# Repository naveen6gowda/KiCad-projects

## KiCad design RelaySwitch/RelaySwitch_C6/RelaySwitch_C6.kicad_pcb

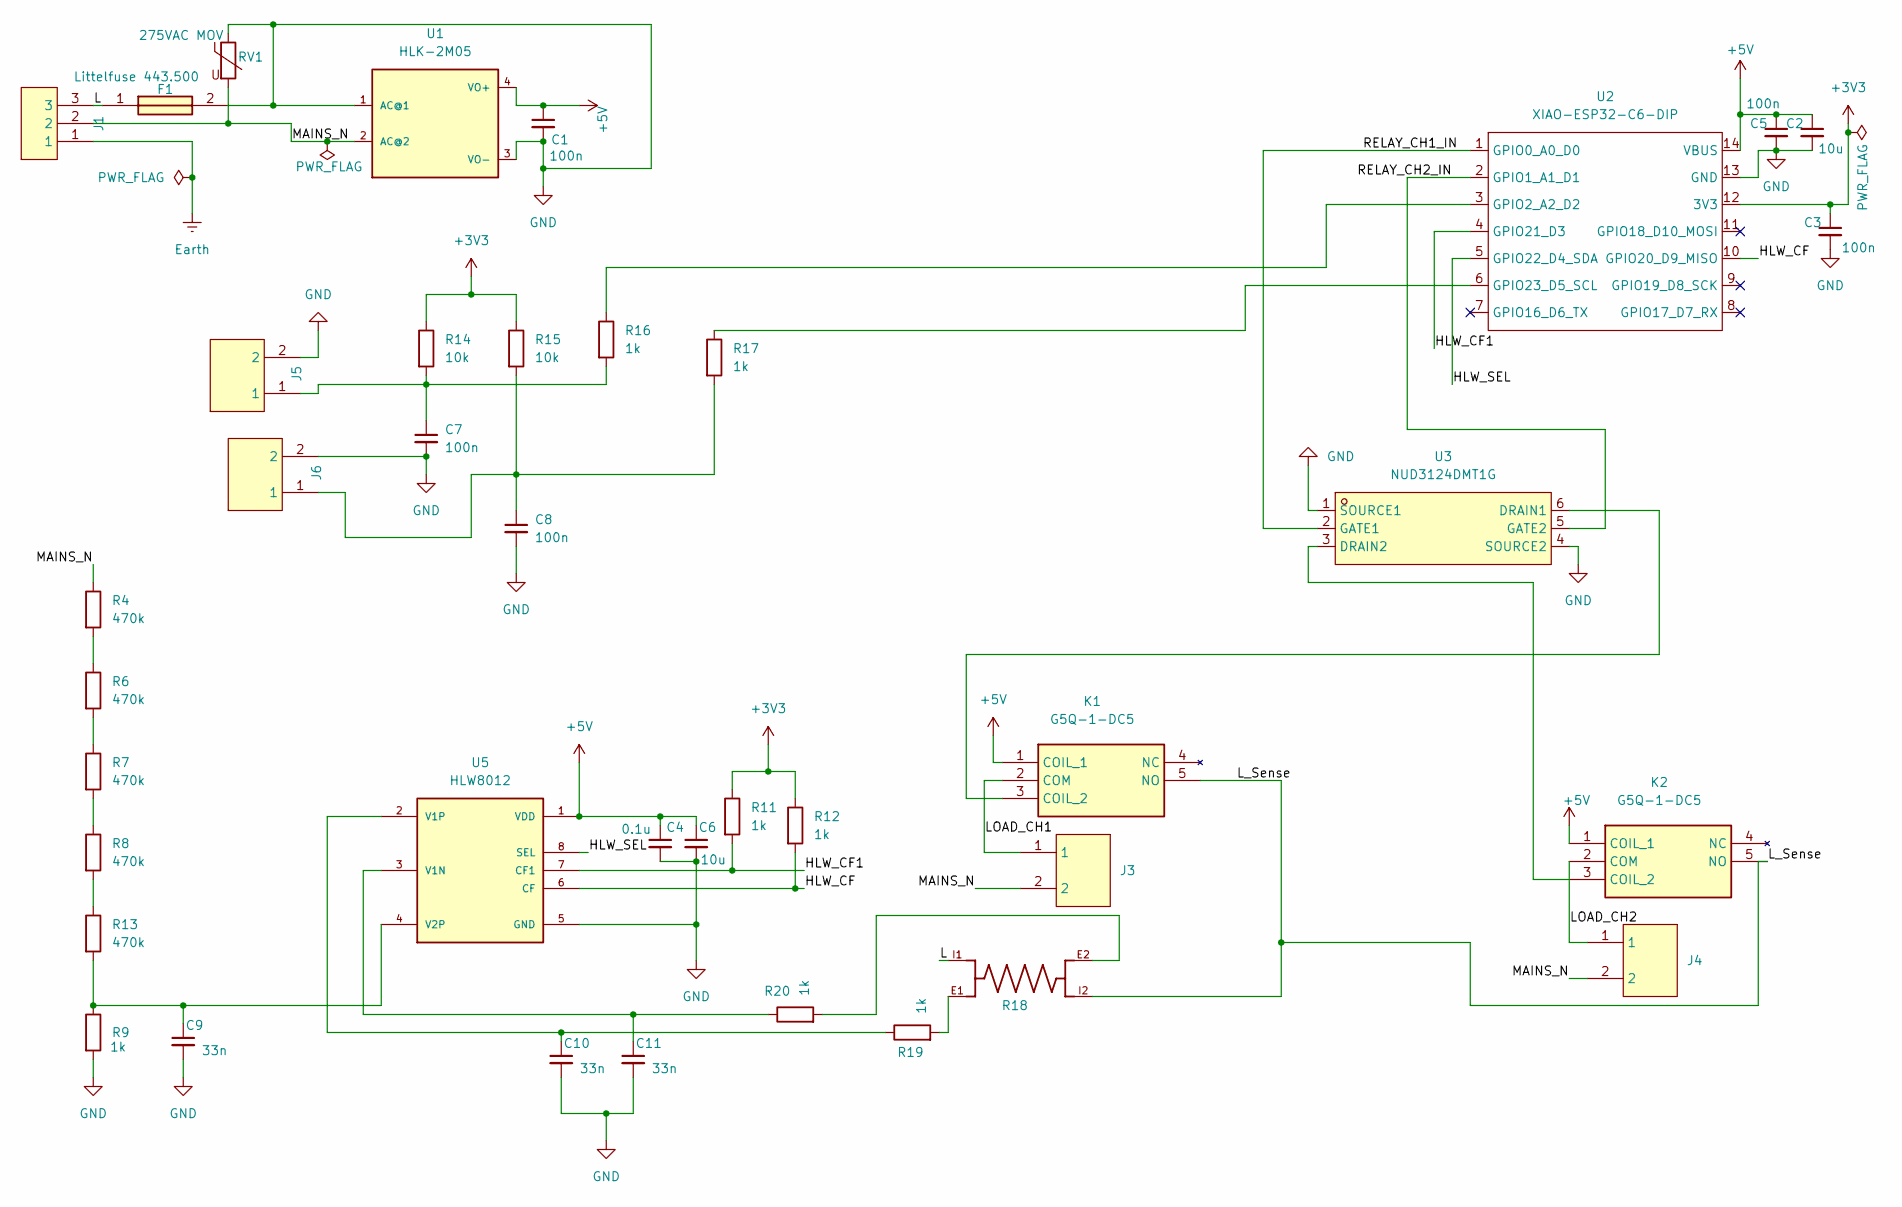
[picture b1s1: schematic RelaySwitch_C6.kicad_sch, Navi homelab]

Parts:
C1, C3, C5, C7, C8: 100n; C_0402_1005Metric
C2: 10u; C_0805_2012Metric
C4: 0.1u; C_0402_1005Metric
C6: 10u; C_0402_1005Metric
C9, C10, C11: 33n; C_0402_1005Metric
F1: Littelfuse 443.500; 0443500DR; Manufacturer_Part_Number 0443.500
J1: AC_MAINS_IN; CONN-TH_3P-P5.00_WJ128V-5.0-3P; DigiKey_Part_Number 2223-TB0011-350-03BE-ND
J3: LOAD_CH1; CONN-TH_2P-P5.00_WJ128V-5.0-2P; PARTREV 1.0; DigiKey_Part_Number 2223-TB0011-350-02BE-ND
J4: LOAD_CH2; CONN-TH_2P-P5.00_WJ128V-5.0-2P; PARTREV 1.0; DigiKey_Part_Number 2223-TB0011-350-02BE-ND
J5: SW1_INPUT; CONN-TH_2P-P5.00_WJ128V-5.0-2P; PARTREV 1.0; DigiKey_Part_Number 2223-TB0011-350-02BE-ND
J6: SW2_INPUT; CONN-TH_2P-P5.00_WJ128V-5.0-2P; PARTREV 1.0; DigiKey_Part_Number 2223-TB0011-350-02BE-ND
K1, K2: G5Q-1-DC5; Relay_SPDT_Omron-G5Q-1; Manufacturer_Part_Number HF3FF/005-1ZST
R4, R6, R7, R8, R13: 470k; R_0402_1005Metric
R9, R11, R12, R16, R17, R19, R20: 1k; R_0402_1005Metric
R14, R15: 10k; R_0402_1005Metric
R18: 1m; RES_WSK2512R0100FEA; PARTREV 04-Apr-2022; DigiKey_Part_Number 541-WSK2512R0100FEACT-ND
RV1: 275VAC MOV; RV_Disc_D7mm_W3.4mm_P5mm
U1: HLK-2M05
U2: XIAO-ESP32-C6-DIP
U3: NUD3124DMT1G; SC-74-6_L3.0-W1.5-P0.95-LS2.8-BL; LCSC Part C182473
U5: HLW8012; SOIC8; M_PART_NUMBER HLW8012

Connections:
+3V3: C3.1, R11.1, R12.1, R14.1, R15.1, U2.12 (3V3)
+5V: C1.1, C2.1, C4.1, C5.1, C6.1, K1.1 (COIL_1), K2.1 (COIL_1), U1.4 (VO+), U2.14 (VBUS), U5.1 (VDD)
/HLW_CF: R12.2, U2.10 (GPIO20_D9_MISO), U5.6 (CF)
/HLW_CF1: R11.2, U2.4 (GPIO21_D3), U5.7 (CF1)
/HLW_SEL: U2.5 (GPIO22_D4_SDA), U5.8 (SEL)
/L: F1.1, J1.3, R18.I1
/LOAD_CH1: J3.1, K1.2 (COM)
/LOAD_CH2: J4.1, K2.2 (COM)
/L_Sense: K1.5 (NO), K2.5 (NO), R18.I2
/MAINS_N: J1.2, J3.2, J4.2, R4.1, RV1.2, U1.2 (AC@2)
/RELAY_CH1_IN: U2.1 (GPIO0_A0_D0), U3.2 (GATE1)
/RELAY_CH2_IN: U2.2 (GPIO1_A1_D1), U3.5 (GATE2)
Earth: J1.1
GND: C1.2, C2.2, C3.2, C4.2, C5.2, C6.2, C7.2, C8.2, C9.2, C10.2, C11.2, F1.2, J5.2, J6.2, R9.2, RV1.1, U1.1 (AC@1), U1.3 (VO-), U2.13 (GND), U3.1 (SOURCE1), U3.4 (SOURCE2), U5.5 (GND)
unnamed: C7.1, J5.1, R14.2, R16.2
unnamed: C8.1, J6.1, R15.2, R17.2
unnamed: K1.3 (COIL_2), U3.6 (DRAIN1)
unnamed: K2.3 (COIL_2), U3.3 (DRAIN2)
unnamed: R4.2, R6.1
unnamed: R6.2, R7.1
unnamed: R7.2, R8.1
unnamed: R8.2, R13.1
unnamed: R18.E1, R19.2
unnamed: R18.E2, R20.2
unnamed: R16.1, U2.3 (GPIO2_A2_D2)
unnamed: R17.1, U2.6 (GPIO23_D5_SCL)
unnamed: C11.1, R20.1, U5.3 (V1N)
unnamed: C10.1, R19.1, U5.2 (V1P)
unnamed: C9.1, R9.1, R13.2, U5.4 (V2P)

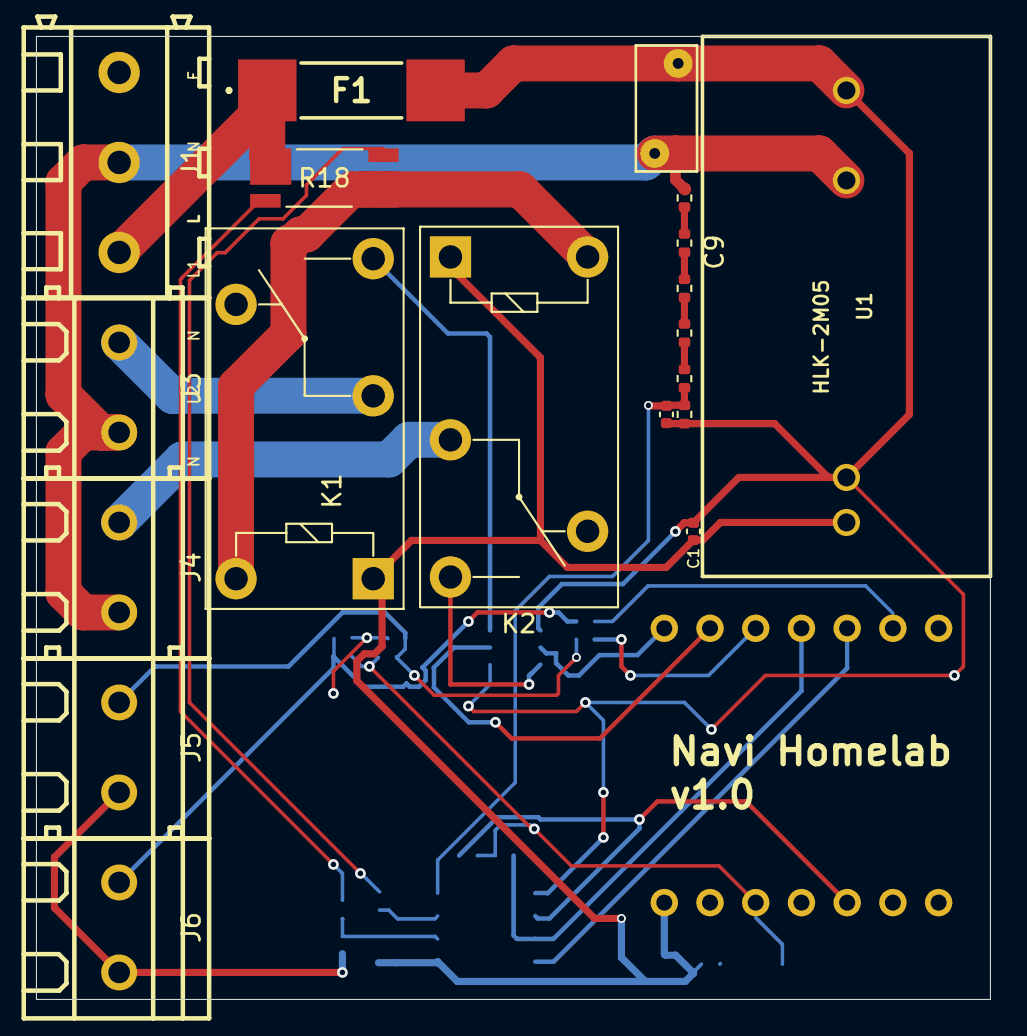
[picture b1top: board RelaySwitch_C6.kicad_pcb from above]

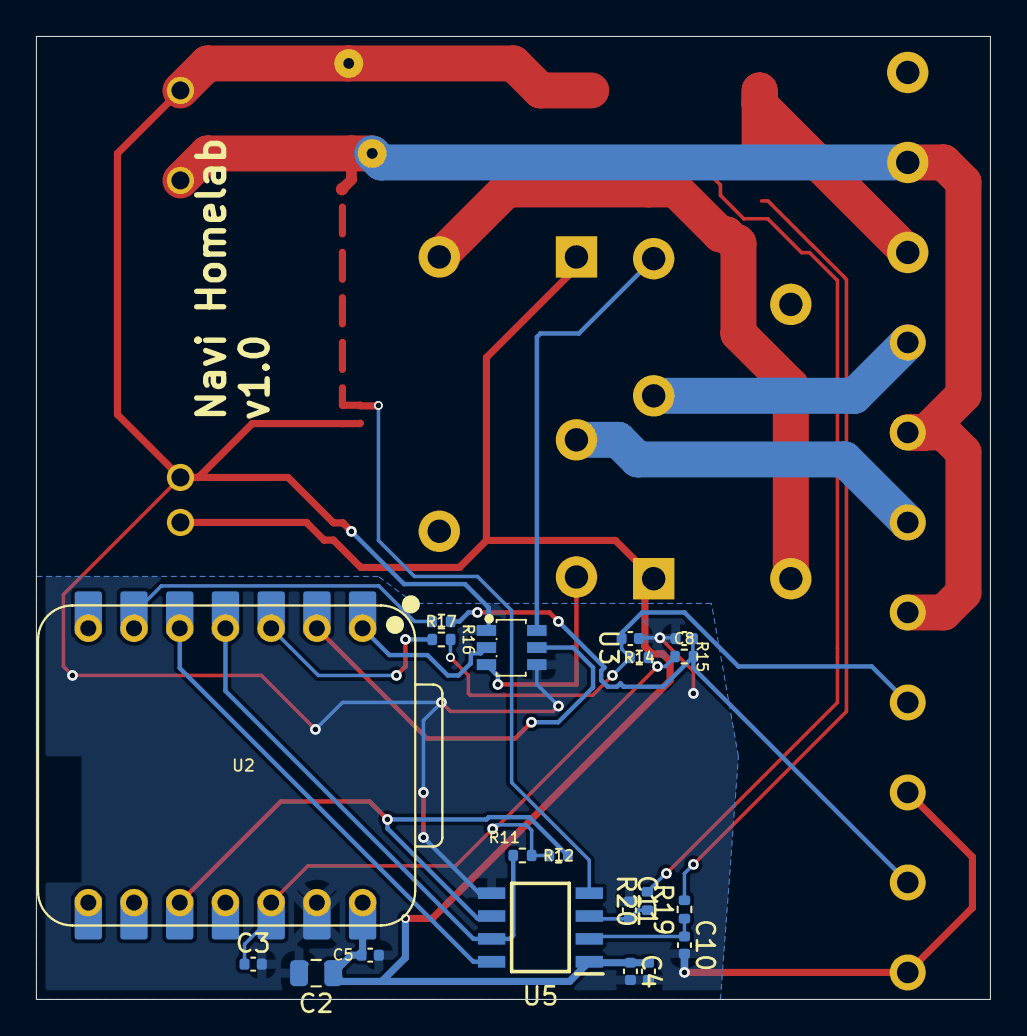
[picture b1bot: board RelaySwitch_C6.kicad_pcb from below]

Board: 2 copper layers, 53.0 x 53.5 mm, 39 parts (20 on the bottom side), 28 nets.

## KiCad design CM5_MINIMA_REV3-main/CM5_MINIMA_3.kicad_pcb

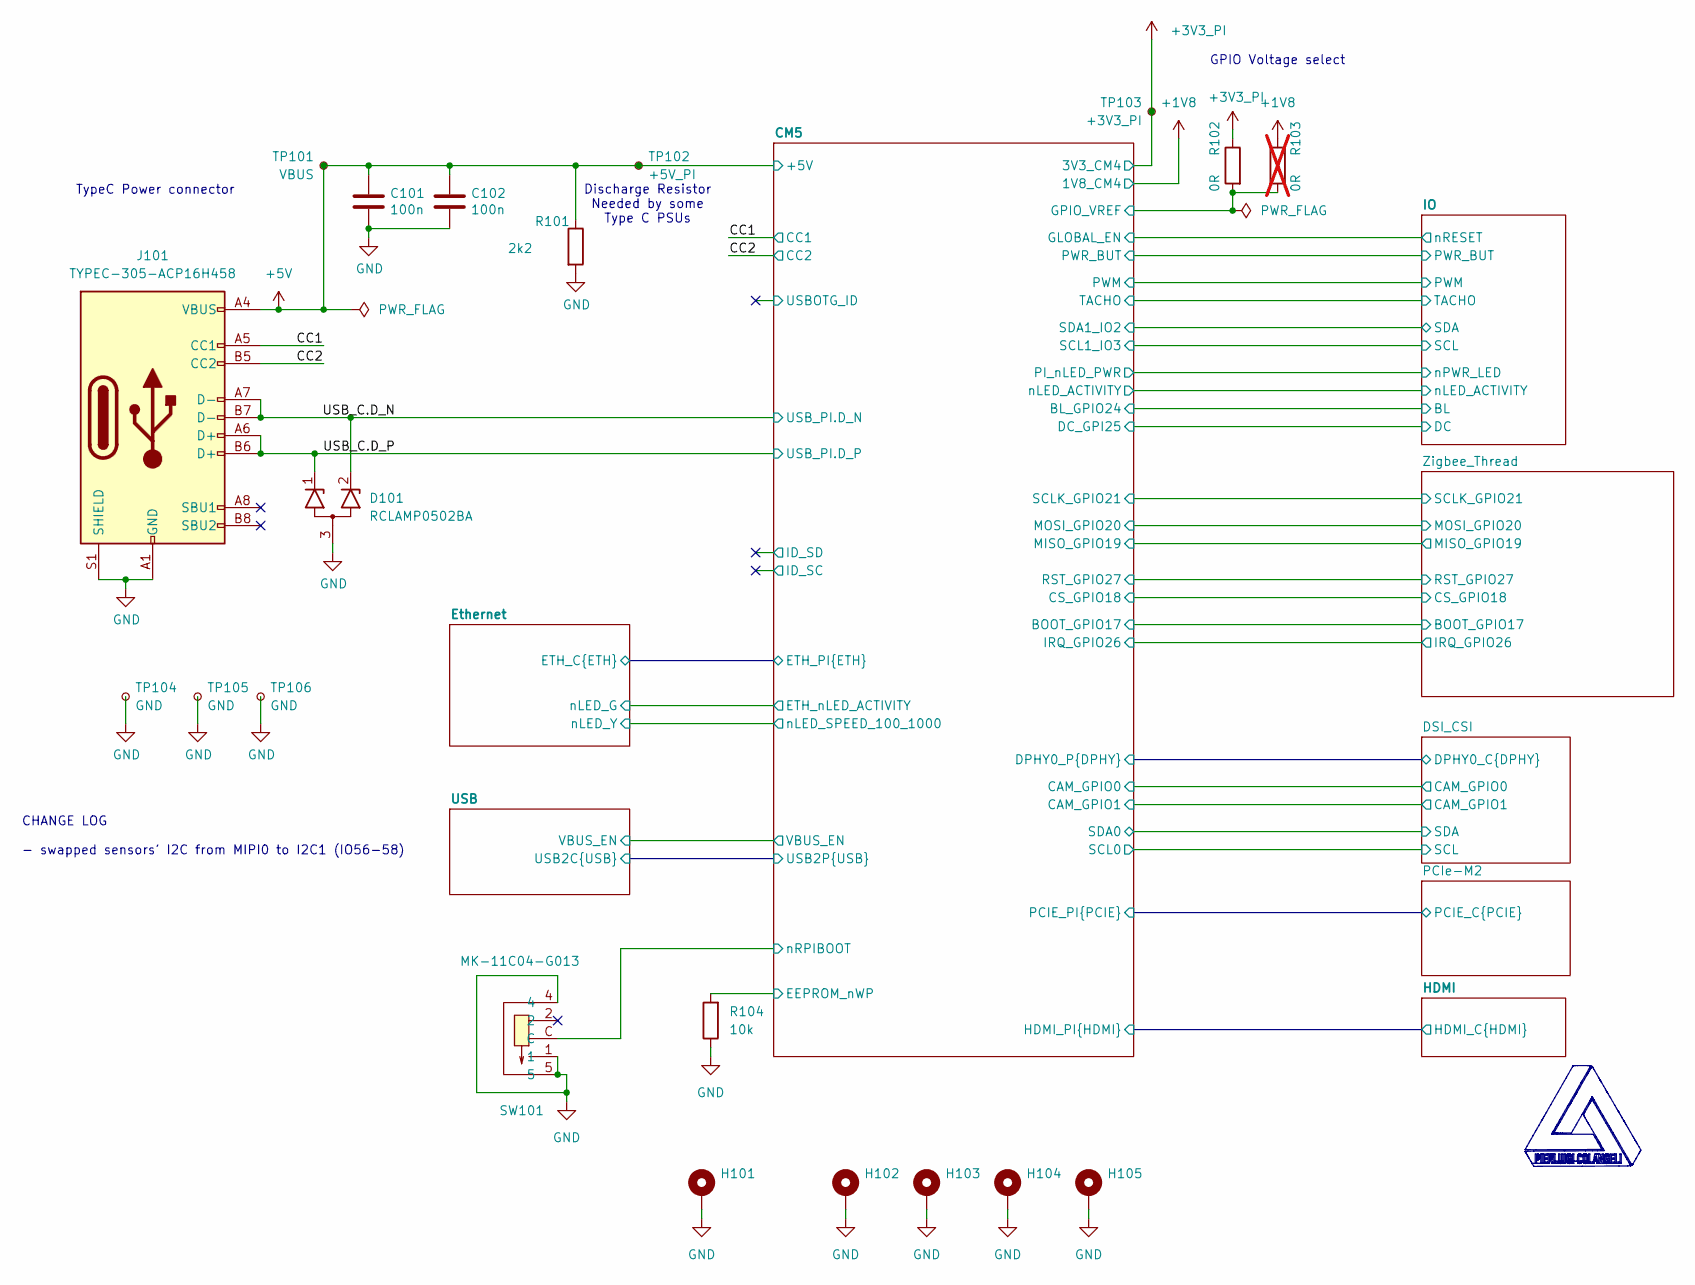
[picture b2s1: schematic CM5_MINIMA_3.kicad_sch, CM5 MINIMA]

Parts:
C101, C102: 100n; C_0402_1005Metric; Part Description 0.1uF 10% 16V Ceramic Capacitor X7R 040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
D101: RCLAMP0502BA; SOT-416
H101: MountingHole_Pad; MountingHole_2.2mm_M2_DIN965_Pad_TopBottom
H102, H103, H104, H105: MountingHole_Pad; MountingHole_2.7mm_Pad
J101: TYPEC-305-ACP16H458; USB-C-SMD_TYPEC-305-ACP16H458; Part Description USBC USB2 data and power connector
R101: 2k2; R_0402_1005Metric
R102: 0R; R_0402_1005Metric; Part Description Resistor 0R M2012 5%
R103: 0R; R_0402_1005Metric; not fitted
R104: 10k; R_0402_1005Metric; LCSC C25744
SW101: MK-11C04-G013; SW-SMD_MK-11C04-G013; LCSC Part C778185
TP101: VBUS; TestPoint_Pad_D1.0mm
TP102: +5V_PI; TestPoint_Pad_D1.0mm
TP103: +3V3_PI; TestPoint_Pad_D1.0mm
TP104, TP105, TP106: GND; TestPoint_THTPad_D1.0mm_Drill0.5mm

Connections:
+1V8: R103.1; also elsewhere on the board
+3V3_PI: R102.1, TP103.1; also elsewhere on the board
+5V: C101.1, C102.1, J101.A4 (VBUS), J101.A9 (VBUS), J101.B4 (VBUS), J101.B9 (VBUS), R101.1, TP101.1, TP102.1; also elsewhere on the board
/CC1: J101.A5 (CC1); also elsewhere on the board
/CC2: J101.B5 (CC2); also elsewhere on the board
/CM5/EEPROM_nWP: R104.2; also elsewhere on the board
/CM5/GPIO_VREF: R102.2, R103.2; also elsewhere on the board
/CM5/nRPIBOOT: SW101.C; also elsewhere on the board
/USB_C.D_N: D101.2 (K2), J101.A7 (D-), J101.B7 (D-); also elsewhere on the board
/USB_C.D_P: D101.1 (K1), J101.A6 (D+), J101.B6 (D+); also elsewhere on the board

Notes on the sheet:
CHANGE LOG - swapped sensors' I2C from MIPI0 to I2C1 (IO56-58)
GPIO Voltage select
TypeC Power connector
Discharge Resistor Needed by some Type C PSUs

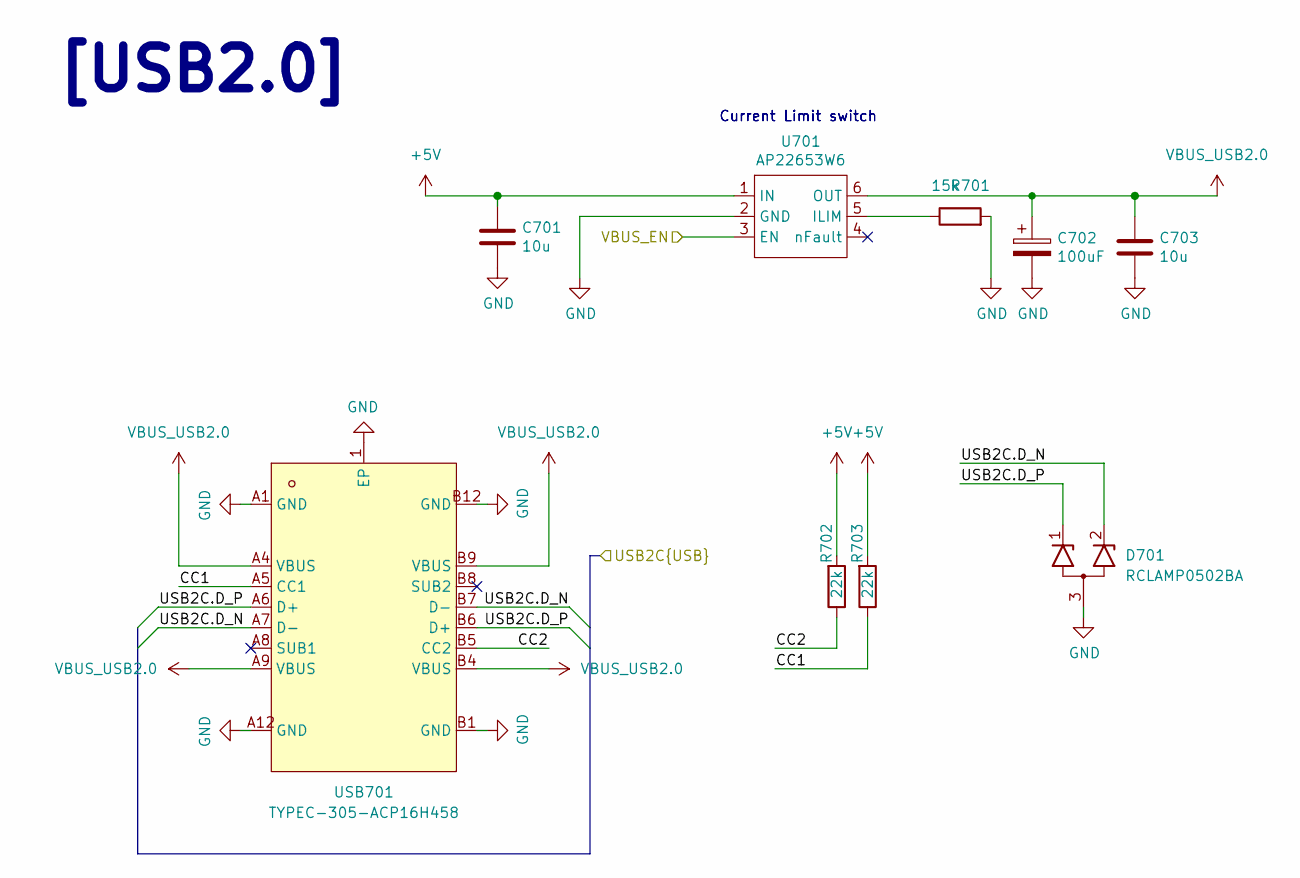
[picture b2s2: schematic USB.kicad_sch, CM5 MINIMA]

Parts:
C701, C703: 10u; C_0805_2012Metric; Part Description 10uF 10% 10V Ceramic Capacitor X7R 0805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; LCSC C15850
C702: 100uF; CP_EIA-3528-21_Kemet-B; Part Description 100uF 6.3V 1.7Ω@100kHz ±10% CASE-B-3528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
D701: RCLAMP0502BA; SOT-416
R701: 15k; R_0402_1005Metric; Part Description Resistor 15K M1005 1% 63mW; LCSC C25756
R702, R703: 22k; R_0402_1005Metric; LCSC C25768
U701: AP22653W6; SOT-23-6; Part Description Power Switch/Driver 1:1 P-Channel 2.1A 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
USB701: TYPEC-305-ACP16H458; USB-C-SMD_TYPEC-305-ACP16H458; LCSC Part C5454943

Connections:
+5V: C701.1, R702.2, R703.2, U701.1 (IN); also elsewhere on the board
/CM5/USB2P.D_N: D701.2 (K2), USB701.A7 (D-), USB701.B7 (D-); also elsewhere on the board
/CM5/USB2P.D_P: D701.1 (K1), USB701.A6 (D+), USB701.B6 (D+); also elsewhere on the board
/CM5/VBUS_EN: U701.3 (EN); also elsewhere on the board
/USB/CC1: R703.1, USB701.A5 (CC1)
/USB/CC2: R702.1, USB701.B5 (CC2)
unnamed: R701.1, U701.5 (ILIM)
VBUS_USB2.0: C702.1, C703.1, U701.6 (OUT), USB701.A4 (VBUS), USB701.A9 (VBUS), USB701.B4 (VBUS), USB701.B9 (VBUS)

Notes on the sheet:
[USB2.0]
Current Limit switch

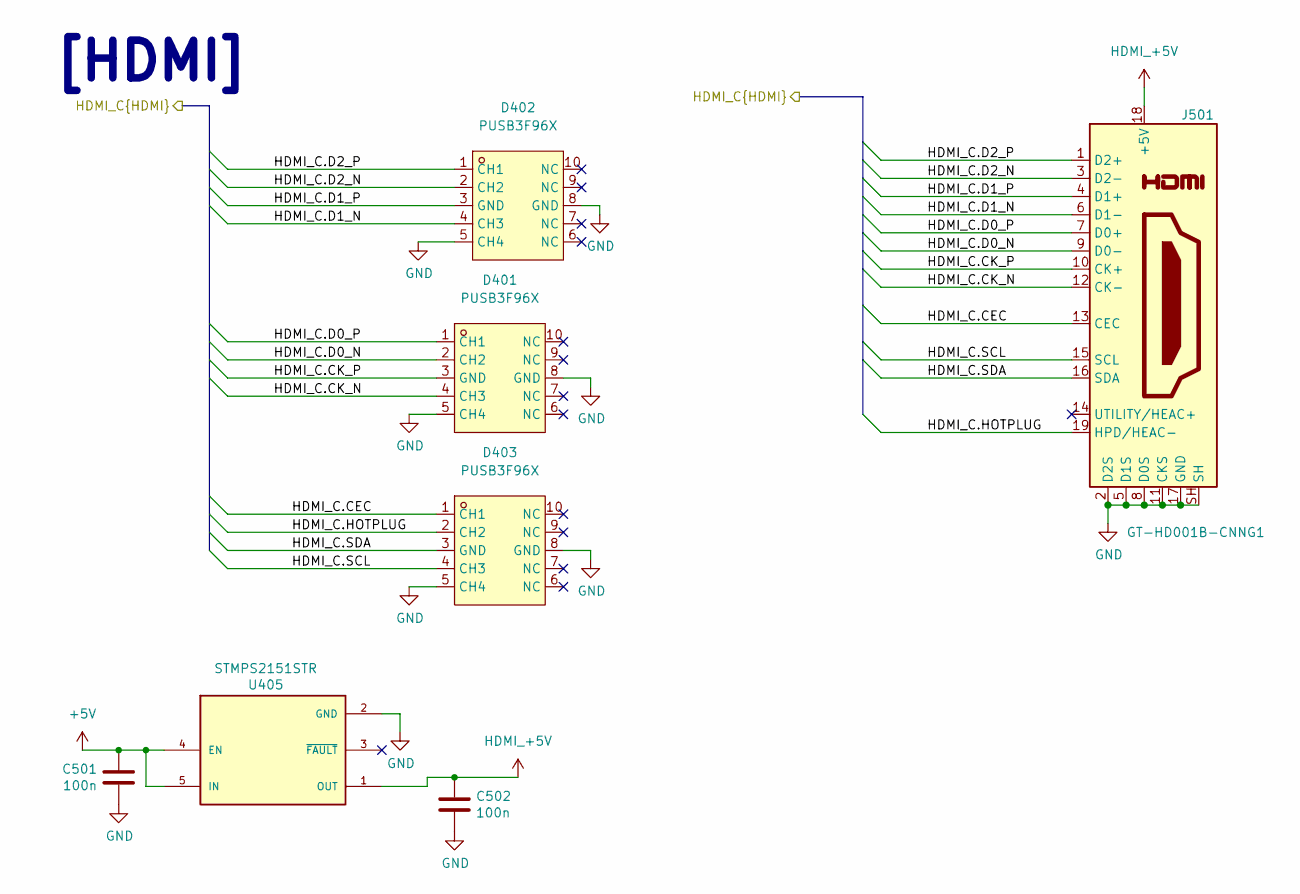
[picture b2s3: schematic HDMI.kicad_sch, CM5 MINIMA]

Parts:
C501, C502: 100n; C_0402_1005Metric; Part Description 0.1uF 10% 16V Ceramic Capacitor X7R 040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
D401, D402, D403: PUSB3F96X; DFN2510A-10_L2.5-W1.0-P0.50-BL; LCSC Part C478121
J501: GT-HD001B-CNNG1; EDAC 690-019-298-412; Part Description HDMI Connector, Right Angle, 19 Contact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
U405: STMPS2151STR; SOT95P280X145-5N; PARTREV 7; LCSC Part C135998

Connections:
+5V: C501.1, U405.4 (EN), U405.5 (VIN); also elsewhere on the board
/CM5/HDMI_PI.CEC: D403.1 (CH1), D403.10 (NC), J501.13 (CEC); also elsewhere on the board
/CM5/HDMI_PI.D0_N: D401.2 (CH2), D401.9 (NC), J501.9 (D0-); also elsewhere on the board
/CM5/HDMI_PI.D0_P: D401.1 (CH1), D401.10 (NC), J501.7 (D0+); also elsewhere on the board
/CM5/HDMI_PI.D2_N: D402.2 (CH2), D402.9 (NC), J501.3 (D2-); also elsewhere on the board
/CM5/HDMI_PI.D2_P: D402.1 (CH1), D402.10 (NC), J501.1 (D2+); also elsewhere on the board
/CM5/HDMI_PI.HOTPLUG: D403.2 (CH2), D403.9 (NC), J501.19 (HPD/HEAC-); also elsewhere on the board
HDMI_+5V: C502.1, J501.18 (+5V), U405.1 (VOUT)

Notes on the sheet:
[HDMI]

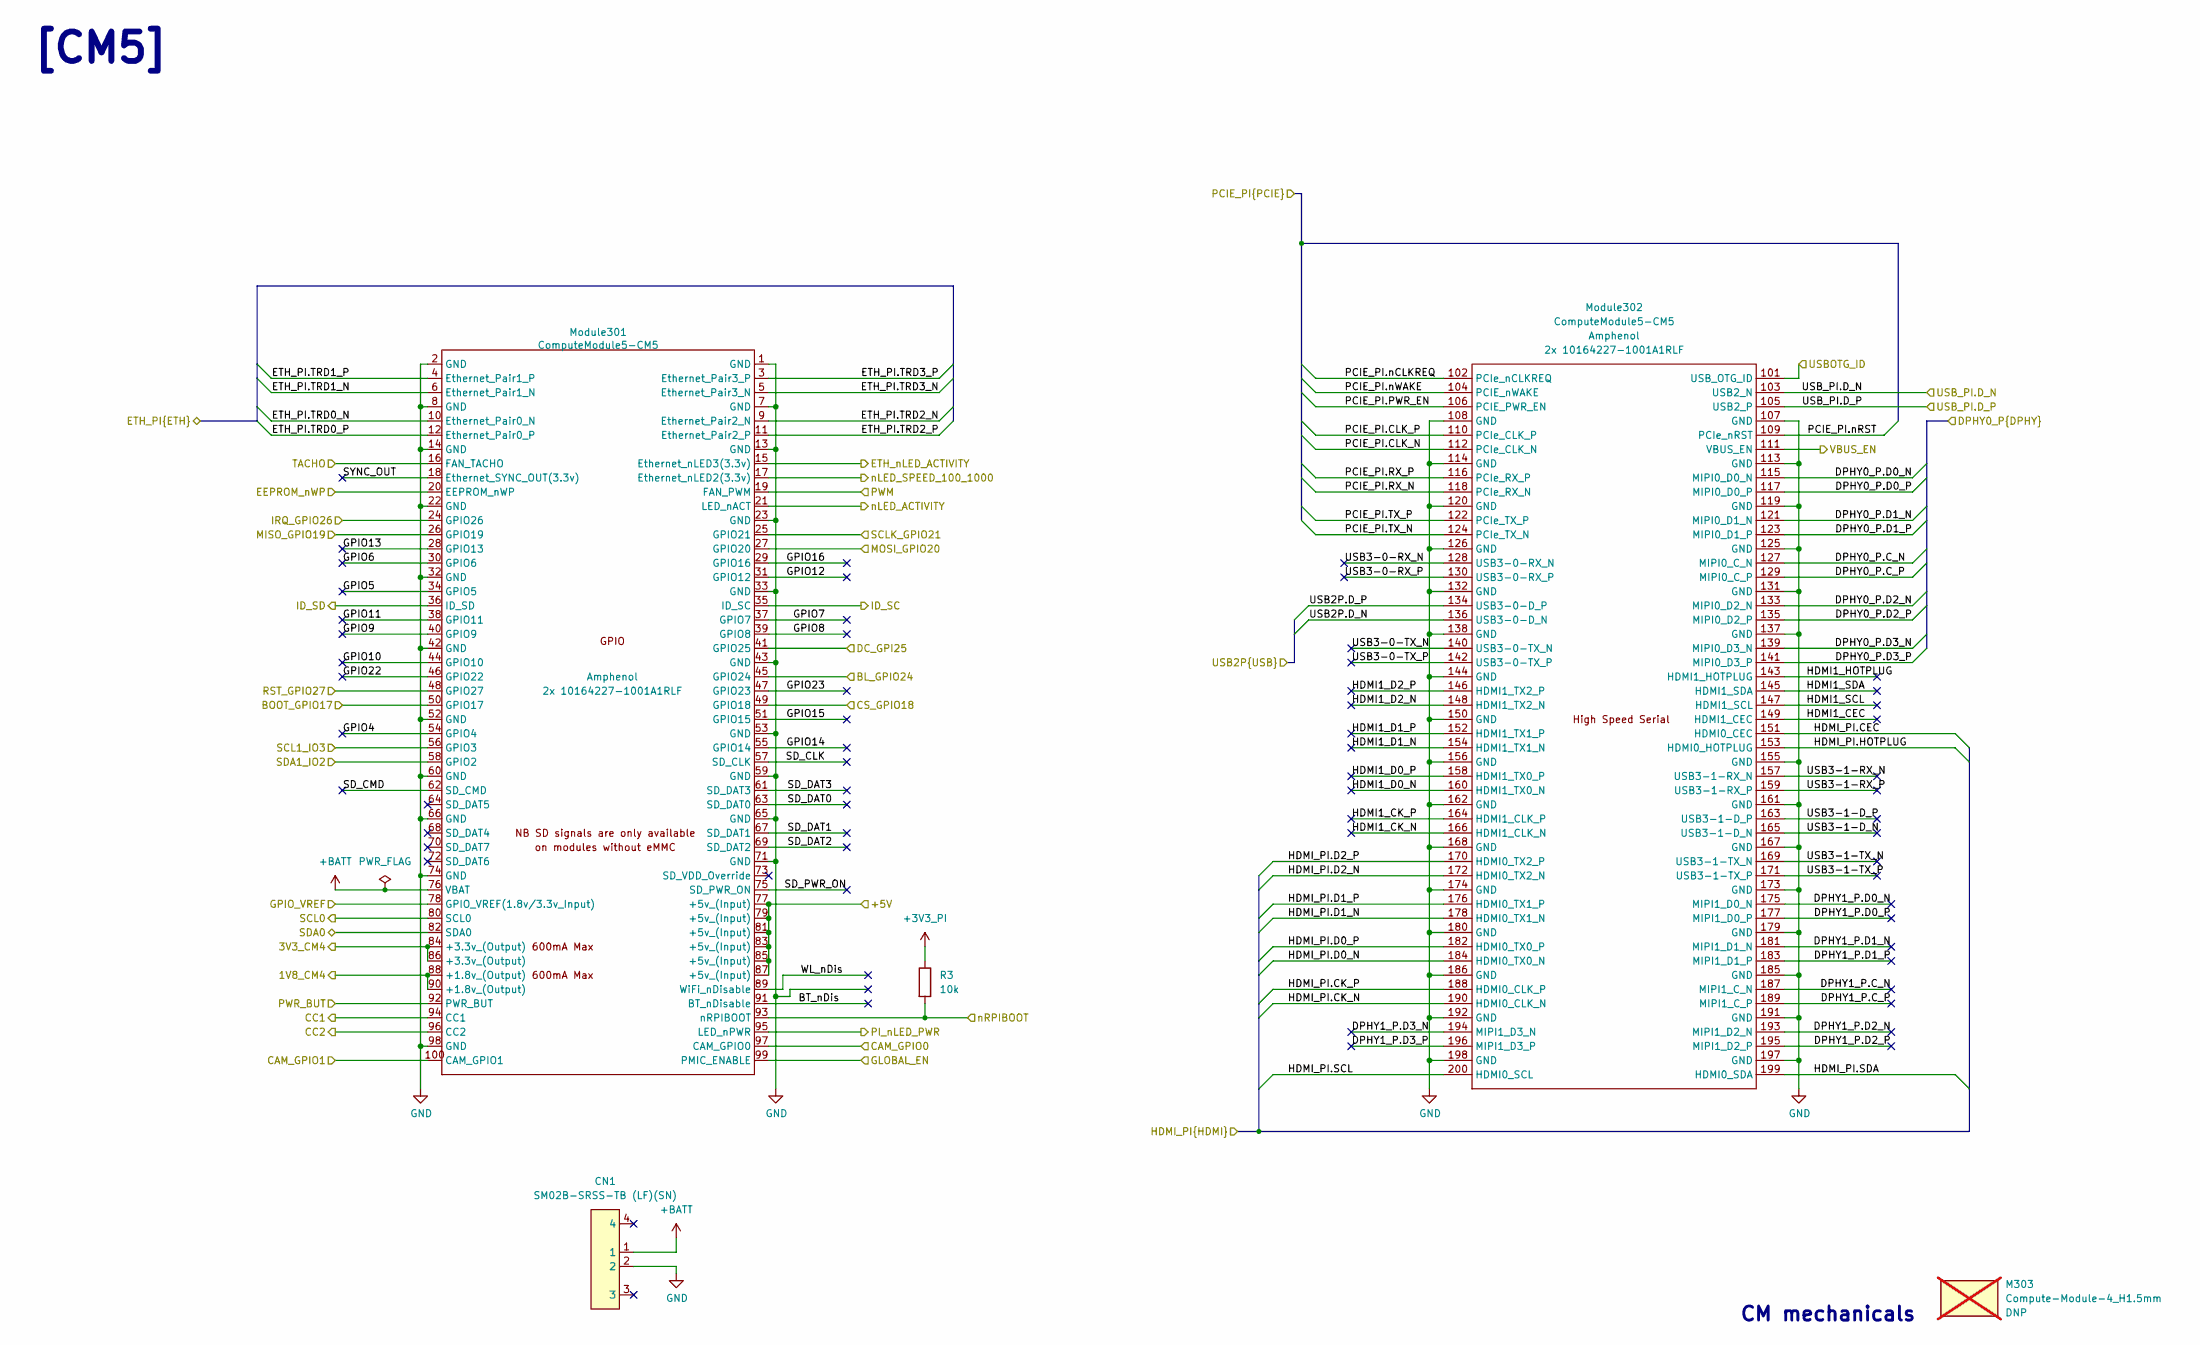
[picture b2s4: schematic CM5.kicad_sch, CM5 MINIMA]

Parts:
CN1: SM02B-SRSS-TB (LF)(SN); CONN-SMD_2P-P1.00_SM02B-SRSS-TB-LF-SN; LCSC Part C160402
M303: Compute-Module-4_H1.5mm; MPN SC0294; not fitted
Module301: ComputeModule5-CM5; Raspberry-Pi-5-Compute-Module_GPIO; Part Description 100 Position Connector Receptacle, Cent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
Module302: ComputeModule5-CM5; Raspberry-Pi-5-Compute-Module_HSS; Part Description 100 Position Connector Receptacle, Cent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
R3: 10k; R_0402_1005Metric

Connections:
+1V8: Module301.88 (+1.8v_(Output)), Module301.90 (+1.8v_(Output)); also elsewhere on the board
+3V3_PI: Module301.84 (+3.3v_(Output)), Module301.86 (+3.3v_(Output)), R3.1; also elsewhere on the board
+5V: Module301.77 (+5v_(Input)), Module301.79 (+5v_(Input)), Module301.81 (+5v_(Input)), Module301.83 (+5v_(Input)), Module301.85 (+5v_(Input)), Module301.87 (+5v_(Input)); also elsewhere on the board
+BATT: CN1.1, Module301.76 (VBAT)
/CC1: Module301.94 (CC1); also elsewhere on the board
/CC2: Module301.96 (CC2); also elsewhere on the board
/CM5/BL_GPIO24: Module301.45 (GPIO24); also elsewhere on the board
/CM5/BOOT_GPIO17: Module301.50 (GPIO17); also elsewhere on the board
/CM5/BT_nDis: Module301.91 (BT_nDisable)
/CM5/CAM_GPIO0: Module301.97 (CAM_GPIO0); also elsewhere on the board
/CM5/CAM_GPIO1: Module301.100 (CAM_GPIO1); also elsewhere on the board
/CM5/CS_GPIO18: Module301.49 (GPIO18); also elsewhere on the board
/CM5/DC_GPI25: Module301.41 (GPIO25); also elsewhere on the board
/CM5/DPHY0_P.C_N: Module302.127 (MIPI0_C_N); also elsewhere on the board
/CM5/DPHY0_P.C_P: Module302.129 (MIPI0_C_P); also elsewhere on the board
/CM5/DPHY0_P.D0_N: Module302.115 (MIPI0_D0_N); also elsewhere on the board
/CM5/DPHY0_P.D0_P: Module302.117 (MIPI0_D0_P); also elsewhere on the board
/CM5/DPHY0_P.D1_N: Module302.121 (MIPI0_D1_N); also elsewhere on the board
/CM5/DPHY0_P.D1_P: Module302.123 (MIPI0_D1_P); also elsewhere on the board
/CM5/DPHY0_P.D2_N: Module302.133 (MIPI0_D2_N); also elsewhere on the board
/CM5/DPHY0_P.D2_P: Module302.135 (MIPI0_D2_P); also elsewhere on the board
/CM5/DPHY0_P.D3_N: Module302.139 (MIPI0_D3_N); also elsewhere on the board
/CM5/DPHY0_P.D3_P: Module302.141 (MIPI0_D3_P); also elsewhere on the board
/CM5/DPHY1_P.C_N: Module302.187 (MIPI1_C_N)
/CM5/DPHY1_P.C_P: Module302.189 (MIPI1_C_P)
/CM5/DPHY1_P.D0_N: Module302.175 (MIPI1_D0_N)
/CM5/DPHY1_P.D0_P: Module302.177 (MIPI1_D0_P)
/CM5/DPHY1_P.D1_N: Module302.181 (MIPI1_D1_N)
/CM5/DPHY1_P.D1_P: Module302.183 (MIPI1_D1_P)
/CM5/DPHY1_P.D2_N: Module302.193 (MIPI1_D2_N)
/CM5/DPHY1_P.D2_P: Module302.195 (MIPI1_D2_P)
/CM5/DPHY1_P.D3_N: Module302.194 (MIPI1_D3_N)
/CM5/DPHY1_P.D3_P: Module302.196 (MIPI1_D3_P)
/CM5/EEPROM_nWP: Module301.20 (EEPROM_nWP); also elsewhere on the board
/CM5/ETH_PI.TRD0_N: Module301.10 (Ethernet_Pair0_N); also elsewhere on the board
/CM5/ETH_PI.TRD0_P: Module301.12 (Ethernet_Pair0_P); also elsewhere on the board
/CM5/ETH_PI.TRD1_N: Module301.6 (Ethernet_Pair1_N); also elsewhere on the board
/CM5/ETH_PI.TRD1_P: Module301.4 (Ethernet_Pair1_P); also elsewhere on the board
/CM5/ETH_PI.TRD2_N: Module301.9 (Ethernet_Pair2_N); also elsewhere on the board
/CM5/ETH_PI.TRD2_P: Module301.11 (Ethernet_Pair2_P); also elsewhere on the board
/CM5/ETH_PI.TRD3_N: Module301.5 (Ethernet_Pair3_N); also elsewhere on the board
/CM5/ETH_PI.TRD3_P: Module301.3 (Ethernet_Pair3_P); also elsewhere on the board
/CM5/ETH_nLED_ACTIVITY: Module301.15 (Ethernet_nLED3(3.3v)); also elsewhere on the board
/CM5/GLOBAL_EN: Module301.99 (PMIC_ENABLE)
/CM5/GPIO4: Module301.54 (GPIO4)
/CM5/GPIO5: Module301.34 (GPIO5)
/CM5/GPIO6: Module301.30 (GPIO6)
/CM5/GPIO7: Module301.37 (GPIO7)
/CM5/GPIO8: Module301.39 (GPIO8)
/CM5/GPIO9: Module301.40 (GPIO9)
/CM5/GPIO10: Module301.44 (GPIO10)
/CM5/GPIO11: Module301.38 (GPIO11)
/CM5/GPIO12: Module301.31 (GPIO12)
/CM5/GPIO13: Module301.28 (GPIO13)
/CM5/GPIO14: Module301.55 (GPIO14)
/CM5/GPIO15: Module301.51 (GPIO15)
/CM5/GPIO16: Module301.29 (GPIO16)
/CM5/GPIO22: Module301.46 (GPIO22)
/CM5/GPIO23: Module301.47 (GPIO23)
/CM5/GPIO_VREF: Module301.78 (GPIO_VREF(1.8v/3.3v_Input)); also elsewhere on the board
/CM5/HDMI1_CEC: Module302.149 (HDMI1_CEC)
/CM5/HDMI1_CK_N: Module302.166 (HDMI1_CLK_N)
/CM5/HDMI1_CK_P: Module302.164 (HDMI1_CLK_P)
/CM5/HDMI1_D0_N: Module302.160 (HDMI1_TX0_N)
/CM5/HDMI1_D0_P: Module302.158 (HDMI1_TX0_P)
/CM5/HDMI1_D1_N: Module302.154 (HDMI1_TX1_N)
/CM5/HDMI1_D1_P: Module302.152 (HDMI1_TX1_P)
/CM5/HDMI1_D2_N: Module302.148 (HDMI1_TX2_N)
/CM5/HDMI1_D2_P: Module302.146 (HDMI1_TX2_P)
/CM5/HDMI1_HOTPLUG: Module302.143 (HDMI1_HOTPLUG)
/CM5/HDMI1_SCL: Module302.147 (HDMI1_SCL)
/CM5/HDMI1_SDA: Module302.145 (HDMI1_SDA)
/CM5/HDMI_PI.CEC: Module302.151 (HDMI0_CEC); also elsewhere on the board
/CM5/HDMI_PI.D0_N: Module302.184 (HDMI0_TX0_N); also elsewhere on the board
/CM5/HDMI_PI.D0_P: Module302.182 (HDMI0_TX0_P); also elsewhere on the board
/CM5/HDMI_PI.D2_N: Module302.172 (HDMI0_TX2_N); also elsewhere on the board
/CM5/HDMI_PI.D2_P: Module302.170 (HDMI0_TX2_P); also elsewhere on the board
/CM5/HDMI_PI.HOTPLUG: Module302.153 (HDMI0_HOTPLUG); also elsewhere on the board
/CM5/ID_SC: Module301.35 (ID_SC)
/CM5/ID_SD: Module301.36 (ID_SD)
/CM5/IRQ_GPIO26: Module301.24 (GPIO26); also elsewhere on the board
/CM5/MISO_GPIO19: Module301.26 (GPIO19); also elsewhere on the board
/CM5/MOSI_GPIO20: Module301.27 (GPIO20); also elsewhere on the board
/CM5/PCIE_PI.CLK_N: Module302.112 (PCIe_CLK_N); also elsewhere on the board
/CM5/PCIE_PI.CLK_P: Module302.110 (PCIe_CLK_P); also elsewhere on the board
/CM5/PCIE_PI.PWR_EN: Module302.106 (PCIE_PWR_EN); also elsewhere on the board
/CM5/PCIE_PI.RX_N: Module302.118 (PCIe_RX_N); also elsewhere on the board
/CM5/PCIE_PI.RX_P: Module302.116 (PCIe_RX_P); also elsewhere on the board
/CM5/PCIE_PI.TX_N: Module302.124 (PCIe_TX_N); also elsewhere on the board
/CM5/PCIE_PI.TX_P: Module302.122 (PCIe_TX_P); also elsewhere on the board
/CM5/PCIE_PI.nCLKREQ: Module302.102 (PCIe_nCLKREQ); also elsewhere on the board
/CM5/PCIE_PI.nRST: Module302.109 (PCIe_nRST); also elsewhere on the board
/CM5/PCIE_PI.nWAKE: Module302.104 (PCIE_nWAKE); also elsewhere on the board
/CM5/PI_nLED_PWR: Module301.95 (LED_nPWR); also elsewhere on the board
/CM5/PWM: Module301.19 (FAN_PWM); also elsewhere on the board
/CM5/PWR_BUT: Module301.92 (PWR_BUT); also elsewhere on the board
/CM5/RST_GPIO27: Module301.48 (GPIO27); also elsewhere on the board
/CM5/SCL0: Module301.80 (SCL0); also elsewhere on the board
/CM5/SCLK_GPIO21: Module301.25 (GPIO21); also elsewhere on the board
/CM5/SDA0: Module301.82 (SDA0); also elsewhere on the board
/CM5/SD_CLK: Module301.57 (SD_CLK)
/CM5/SD_CMD: Module301.62 (SD_CMD)
/CM5/SD_DAT0: Module301.63 (SD_DAT0)
/CM5/SD_DAT1: Module301.67 (SD_DAT1)
/CM5/SD_DAT2: Module301.69 (SD_DAT2)
/CM5/SD_DAT3: Module301.61 (SD_DAT3)
/CM5/SD_PWR_ON: Module301.75 (SD_PWR_ON)
/CM5/SYNC_OUT: Module301.18 (Ethernet_SYNC_OUT(3.3v))
/CM5/TACHO: Module301.16 (FAN_TACHO); also elsewhere on the board
/CM5/USB2P.D_N: Module302.136 (USB3-0-D_N); also elsewhere on the board
/CM5/USB2P.D_P: Module302.134 (USB3-0-D_P); also elsewhere on the board
/CM5/USB3-0-RX_N: Module302.128 (USB3-0-RX_N)
/CM5/USB3-0-RX_P: Module302.130 (USB3-0-RX_P)
/CM5/USB3-0-TX_N: Module302.140 (USB3-0-TX_N)
/CM5/USB3-0-TX_P: Module302.142 (USB3-0-TX_P)
/CM5/USB3-1-D_N: Module302.165 (USB3-1-D_N)
/CM5/USB3-1-D_P: Module302.163 (USB3-1-D_P)
/CM5/USB3-1-RX_N: Module302.157 (USB3-1-RX_N)
/CM5/USB3-1-RX_P: Module302.159 (USB3-1-RX_P)
/CM5/USB3-1-TX_N: Module302.169 (USB3-1-TX_N)
/CM5/USB3-1-TX_P: Module302.171 (USB3-1-TX_P)
/CM5/USBOTG_ID: Module302.101 (USB_OTG_ID)
/CM5/VBUS_EN: Module302.111 (VBUS_EN); also elsewhere on the board
/CM5/WL_nDis: Module301.89 (WiFi_nDisable)
/CM5/nLED_ACTIVITY: Module301.21 (LED_nACT); also elsewhere on the board
/CM5/nLED_SPEED_100_1000: Module301.17 (Ethernet_nLED2(3.3v)); also elsewhere on the board
/CM5/nRPIBOOT: Module301.93 (nRPIBOOT), R3.2; also elsewhere on the board
/IO/SCL: Module301.56 (GPIO3); also elsewhere on the board
/IO/SDA: Module301.58 (GPIO2); also elsewhere on the board
/USB_C.D_N: Module302.103 (USB2_N); also elsewhere on the board
/USB_C.D_P: Module302.105 (USB2_P); also elsewhere on the board

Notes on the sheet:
CM mechanicals
[CM5]

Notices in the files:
parts and their libraries:
License: Apache-2.0
